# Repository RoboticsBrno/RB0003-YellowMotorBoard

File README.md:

# RB0003-YellowMotorBoard
Motor board with encoder sensors for yellow motor.

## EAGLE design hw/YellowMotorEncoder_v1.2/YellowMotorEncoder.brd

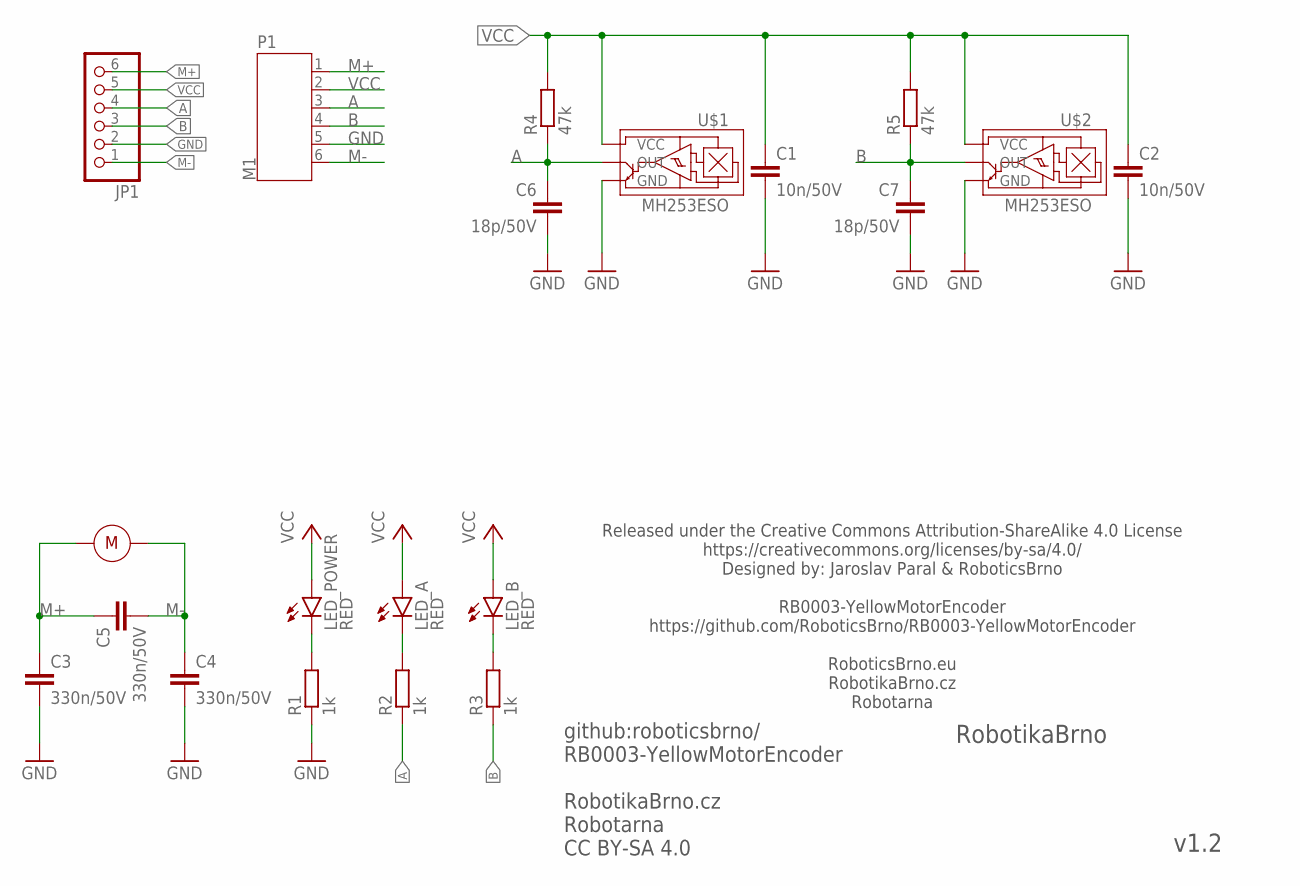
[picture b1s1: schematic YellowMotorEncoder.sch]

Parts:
C1, C2: 10n/50V; C0402; LCSC_ID C15195
C3, C4, C5: 330n/50V; C0805; LCSC_ID C1740
C6, C7: 18p/50V; C0402; LCSC_ID C1549
JP1: PINHD-1X6; 1X06
LED_A: RED; CHIPLED_0603; DIGIKEY 160-1446-1-ND
LED_B: RED; CHIPLED_0603; DIGIKEY 160-1446-1-ND
LED_POWER: RED; CHIPLED_0603; DIGIKEY 160-1446-1-ND
P1: M1; JST-PH6
R1, R2, R3: 1k; R0603; LCSC_ID C21190
R4, R5: 47k; R0603; LCSC_ID C25819
U$1, U$2: MH253ESO; SOT23
U$3: YELLOW_MOTOR

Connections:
A: C6.1, JP1.4, P1.3, R2.1, R4.1, U$1.2 (OUT)
B: C7.1, JP1.3, P1.4, R3.1, R5.1, U$2.2 (OUT)
GND: C1.2, C2.2, C3.2, C4.2, C6.2, C7.2, JP1.2, P1.5, R1.1, U$1.3 (GND), U$2.3 (GND)
LED_POWER: LED_POWER.C, R1.2
LED_SIDE1: LED_A.C, R2.2
LED_TOP1: LED_B.C, R3.2
M+: C3.1, C5.1, JP1.6, P1.1, U$3.P$2
M-: C4.1, C5.2, JP1.1, P1.6, U$3.P$1
VCC: C1.1, C2.1, JP1.5, LED_A.A, LED_B.A, LED_POWER.A, P1.2, R4.2, R5.2, U$1.1 (VCC), U$2.1 (VCC)

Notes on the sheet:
github:roboticsbrno/ RB0003-YellowMotorEncoder RobotikaBrno.cz Robotarna CC BY-SA 4.0
RobotikaBrno
v1.2
Released under the Creative Commons Attribution-ShareAlike 4.0 License https://creativecommons.org/licenses/by-sa/4.0/ Designed by: Jaroslav Paral & RoboticsBrno RB0003-YellowMotorEncoder https://github.com/RoboticsBrno/RB0003-YellowMotorEncoder RoboticsBrno.eu RobotikaBrno.cz Robotarna

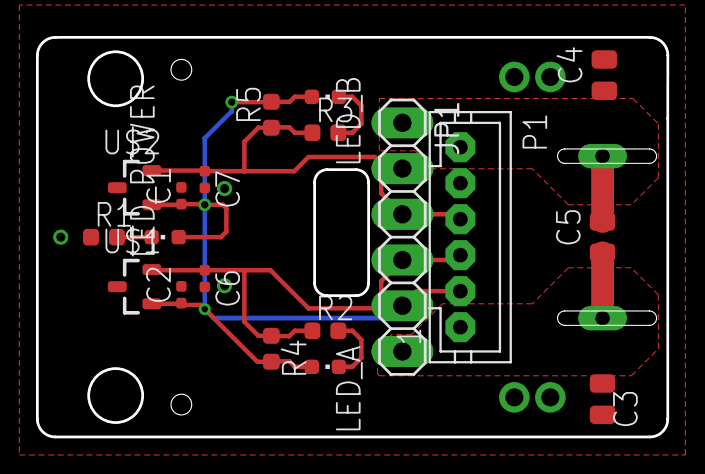
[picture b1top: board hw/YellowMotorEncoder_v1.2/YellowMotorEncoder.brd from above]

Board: 2 copper layers, 35.0 x 22.2 mm, 20 parts (0 on the bottom side), 9 nets.

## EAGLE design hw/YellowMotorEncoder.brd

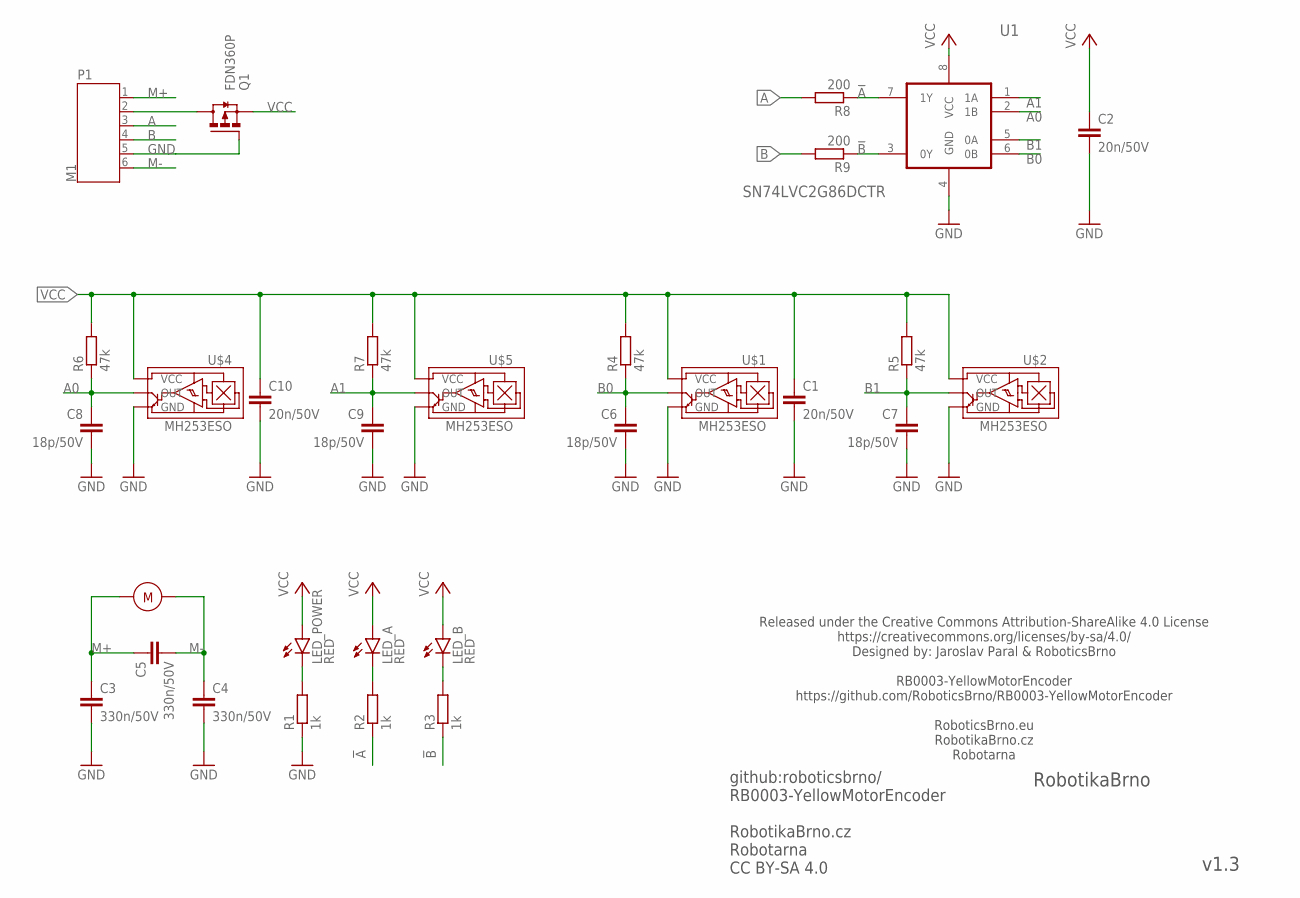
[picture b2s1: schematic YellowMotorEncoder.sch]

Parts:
C1, C2, C10: 20n/50V; C0402; LCSC_ID C15195
C3, C4, C5: 330n/50V; C0805; LCSC_ID C1740
C6, C7, C8, C9: 18p/50V; C0402; LCSC_ID C1549
LED_A: RED; CHIPLED_0603; DIGIKEY 160-1446-1-ND
LED_B: RED; CHIPLED_0603; DIGIKEY 160-1446-1-ND
LED_POWER: RED; CHIPLED_0603; DIGIKEY 160-1446-1-ND
M1: YELLOW_MOTORV2; YELLOW_MOTOR_V2
P1: M1; JST-PH6
Q1: FDN360P; SUPER-SOT3
R1, R2, R3: 1k; R0402; LCSC_ID C21190
R4, R5, R6, R7: 47k; R0402; LCSC_ID C25819
R8, R9: 200; R0402; LCSC_ID C25819
U1: SN74LVC2G86DCTR; SOP65P400X130-8N
U$1, U$2, U$4, U$5: MH253ESO; SOT23

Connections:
!A: R2.1, R8.1, U1.7 (1Y)
!B: R3.1, R9.1, U1.3 (0Y)
A: P1.3, R8.2
A0: C8.1, R6.1, U1.2 (1B), U$4.2 (OUT)
A1: C9.1, R7.1, U1.1 (1A), U$5.2 (OUT)
B: P1.4, R9.2
B0: C6.1, R4.1, U1.6 (0B), U$1.2 (OUT)
B1: C7.1, R5.1, U1.5 (0A), U$2.2 (OUT)
GND: C1.2, C2.2, C3.2, C4.2, C6.2, C7.2, C8.2, C9.2, C10.2, P1.5, Q1.1 (G), R1.1, U1.4 (GND), U$1.3 (GND), U$2.3 (GND), U$4.3 (GND), U$5.3 (GND)
LED_POWER: LED_POWER.C, R1.2
LED_SIDE1: LED_A.C, R2.2
LED_TOP1: LED_B.C, R3.2
M+: C3.1, C5.1, M1.P$1, P1.1
M-: C4.1, C5.2, M1.P$2, P1.6
unnamed: P1.2, Q1.3 (D)
VCC: C1.1, C2.1, C10.1, LED_A.A, LED_B.A, LED_POWER.A, Q1.2 (S), R4.2, R5.2, R6.2, R7.2, U1.8 (VCC), U$1.1 (VCC), U$2.1 (VCC), U$4.1 (VCC), U$5.1 (VCC)

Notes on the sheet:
github:roboticsbrno/ RB0003-YellowMotorEncoder RobotikaBrno.cz Robotarna CC BY-SA 4.0
RobotikaBrno
v1.3
Released under the Creative Commons Attribution-ShareAlike 4.0 License https://creativecommons.org/licenses/by-sa/4.0/ Designed by: Jaroslav Paral & RoboticsBrno RB0003-YellowMotorEncoder https://github.com/RoboticsBrno/RB0003-YellowMotorEncoder RoboticsBrno.eu RobotikaBrno.cz Robotarna

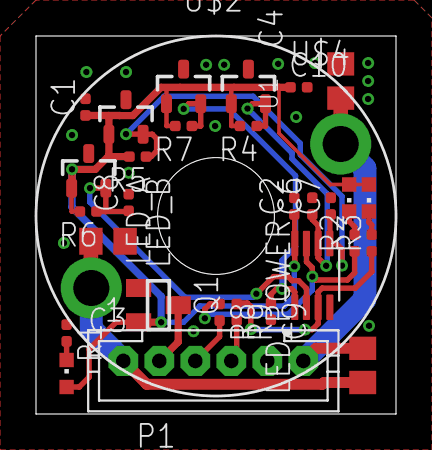
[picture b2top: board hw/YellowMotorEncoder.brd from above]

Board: 2 copper layers, 20.0 x 21.0 mm, 30 parts (0 on the bottom side), 16 nets.

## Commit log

2020-05-08 Add YellowMotorBoard board
    - need to finish routing
2020-05-08 Finish routing of the board
2020-05-09 Finish routing YellowMotorEncoder v1.0
    - route PCB
    - correct position of mounting holes
    - fix connectors signal
2020-05-11 Swap encoder power polarity
2020-05-11 Fixed LEDs orientation
2020-05-11 Rerouted board
2020-05-11 Improve layout for manufacturing
    - add JLC order number to silkscreen
    - add JLC tooling holes
    - fix rotation of hall sensors (`hall_sensor.lbr`)
    - decrease size of silkscreen text- board name, version, licence and URL
2020-05-24 Add and move motor polygons
    - add bottom polygons for motor pins/soldering holes
    - move unmask polygons for motor pads to not overlap with M+/M-
2020-05-24 Change license from `CC0-1.0` to `CC BY-SA 4.0`
2020-05-24 Update/add licenses and authors in libraries
    - not update the libraries inside `.brd` and `.sch` project files
2020-05-24 Create folder `YellowMotorBoard_v1.0` with manufactured Eagle PCB files
2020-05-24 Create version 1.1 - change shape of the motor holes/pads
    - create folder `YellowMotorBoard_v1.1` with manufactured Eagle PCB files
    - shape of motor holes (slotted holes) create according these tutorials
    - https://www.autodesk.com/products/eagle/blog/what-you-didnt-know-about-eagle-slotted-holes/
    - http://blog.snapeda.com/2019/05/30/how-snapeda-creates-slotted-holes-on-eagle/
    - `YellowMotorEncoder_JLCPCB.cam`
    - add Milling (46) layer
2020-06-14 Make many improvements according testing v1.0 and v1.1 boards
    - increase version number from v1.1 to v1.2
    - decrease width of board from 22.4 to 22.2 mm
    - move all parts to corresponding position with respect to the board center
    - move hall sensor:
    - Y axis: 0.25 mm closer to the center of board (distance between both sensors is -0.5 mm)
    - X axis: 0.8 mm in motor direction
2020-06-15 Add Kicad export and KiKit panelizer makefile
    - fix position of text labels "A", "B"
    - export project to Kicad and panelize with KiKit
    - add configuration for TravisCI web page build
2020-06-15 Fix radius in Makefile for KiKit panelization
    - `radius` must be smaller then `space` / 2, NOT smaller or equal
2020-06-22 Improve Makefile and add F.Mask polygon to kicad_export board
2020-06-24 Update shape of motor's slotted holes in Kicad exported board
    - change the shape from circle to oval as this feature is supported in Kicad
    - fix missing capacitor in KiKit export - move their label inside PCB border
2020-06-26 Release/manufacture version 1.2
    Summary:
    - decrease width of the board from 22.4 to 22.2 mm
    - move hall sensor:
    - Y axis: 0.25 mm closer to the centre of the board (distance between both sensors is -0.5 mm)
    - X axis: 0.8 mm in motor direction
    - move slotted holes for motor contact soldering approx. 0.5 mm far from hall sensors for better assembly
2020-07-01 Deploy RoboticsBrno/RB0003-YellowMotorEncoder to github.com/RoboticsBrno/RB0003-YellowMotorEncoder.git:gh-pages
2020-09-20 FourProbes
2020-09-20 librarys
2020-09-20 ochrany
2020-10-14 YellowMotorEncoder_V2.0
    New design with four sensors and xor to combine two signals to one.
    Design is in KiCad.
2020-10-14 3D_viewer
    i add 3d model of motor and connector
2020-10-15 .pro
    i add missing soubor
2020-10-16 rotate sensors
    I changing position of sensors and rotating it in circle around hole for shaft of motor.

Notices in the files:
hw/YellowMotorEncoder_v1.2/YellowMotorEncoder.brd:
v1.2 CC BY-SA 4.0
